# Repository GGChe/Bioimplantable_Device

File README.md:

# Bioimplantable_Device

For a brain implant, there are several limitations in terms of size, power and mechanical properties that may be considered. With the use of optoelectronic techniques, we achieved an ultra-small and fully implantable device that could be used for neurostimulation techniques. Moreover, a Wireless Power Transfer (WPT) system for powering the final LED was also devised to provide a demonstration. The proposed design in this study combines optimal size and practicality given the mechanical constraints of this implant typology. We have applied a modular design approach to the design of this device considering three modules: antenna, conditioner circuit and shank. The implant was designed by using a flexible substrate such as Polyimide. Thin biocompatible encapsulation was also provided for chronic implantation. In addition, simulation of mechanical forces acting on the implant and shank will be carried out to validate a viable shank conformation-encapsulation combination that will safely work under operational stress with a satisfactory margin of safety.

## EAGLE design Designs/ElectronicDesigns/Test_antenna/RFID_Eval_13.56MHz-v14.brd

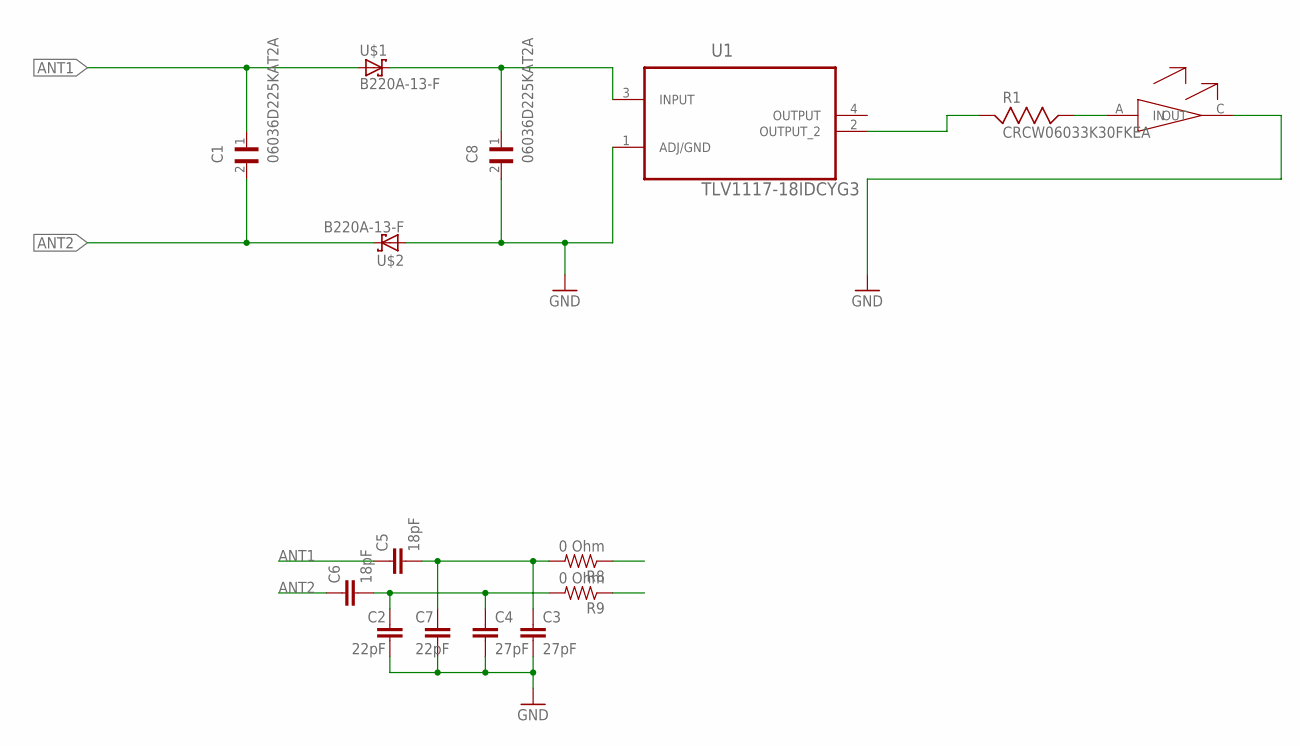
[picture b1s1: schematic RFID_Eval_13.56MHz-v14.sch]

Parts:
C1, C8: 06036D225KAT2A; CAPC1608X90
C2, C7: 22pF; 0402-CAP
C3, C4: 27pF; 0402-CAP
C5, C6: 18pF; 0402-CAP
R1: CRCW06033K30FKEA; RESC1608X55
R8, R9: 0 Ohm; 0402-RES
U1: TLV1117-18IDCYG3; SOT230P700X180-4N
U$1, U$2: B220A-13-F; SMA-DIODE
U$3: LED; LEDM1608X80

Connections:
ANT1: C1.1, C5.1, U$1.1 (A)
ANT2: C1.2, C6.1, U$2.2 (C)
GND: C2.2, C3.2, C4.2, C7.2, C8.2, U1.1 (ADJ/GND), U$2.1 (A), U$3.C (OUT)
unnamed: R1.1, U1.2 (OUTPUT_2)
unnamed: R1.2, U$3.A (IN)
unnamed: C8.1, U1.3 (INPUT), U$1.2 (C)
unnamed: C3.1, C5.2, C7.1, R8.2
unnamed: C2.1, C4.1, C6.2, R9.2

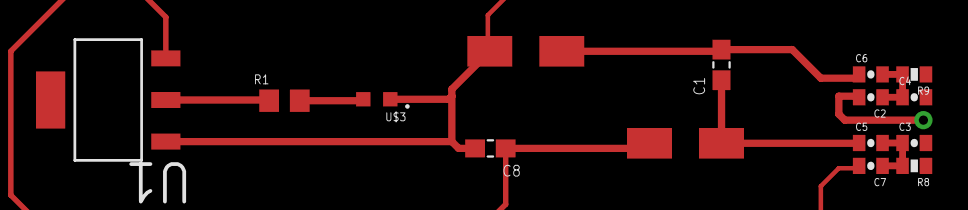
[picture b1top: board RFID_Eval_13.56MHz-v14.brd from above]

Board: 2 copper layers, 15 parts (0 on the bottom side), 8 nets.

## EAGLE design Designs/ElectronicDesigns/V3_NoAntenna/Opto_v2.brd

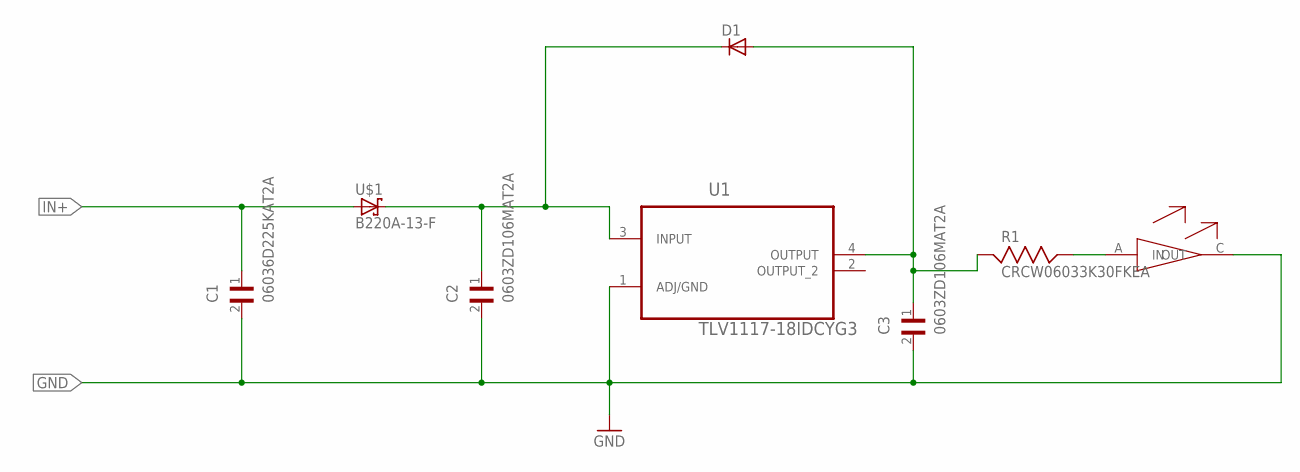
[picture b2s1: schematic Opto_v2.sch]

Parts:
C1: 06036D225KAT2A; CAPC1608X90
C2, C3: 0603ZD106MAT2A; CAPC1608X90
D1: BYS10; SOD106A
R1: CRCW06033K30FKEA; RESC1608X55
U1: TLV1117-18IDCYG3; SOT230P700X180-4N
U$1: B220A-13-F; SMA-DIODE
U$3: LED; LEDM1608X80

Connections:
GND: C1.2, C2.2, C3.2, U1.1 (ADJ/GND), U$3.C (OUT)
IN+: C1.1, U$1.1 (A)
unnamed: R1.2, U$3.A (IN)
unnamed: C3.1, D1.A, R1.1, U1.4 (OUTPUT)
unnamed: C2.1, D1.K, U1.3 (INPUT), U$1.2 (C)

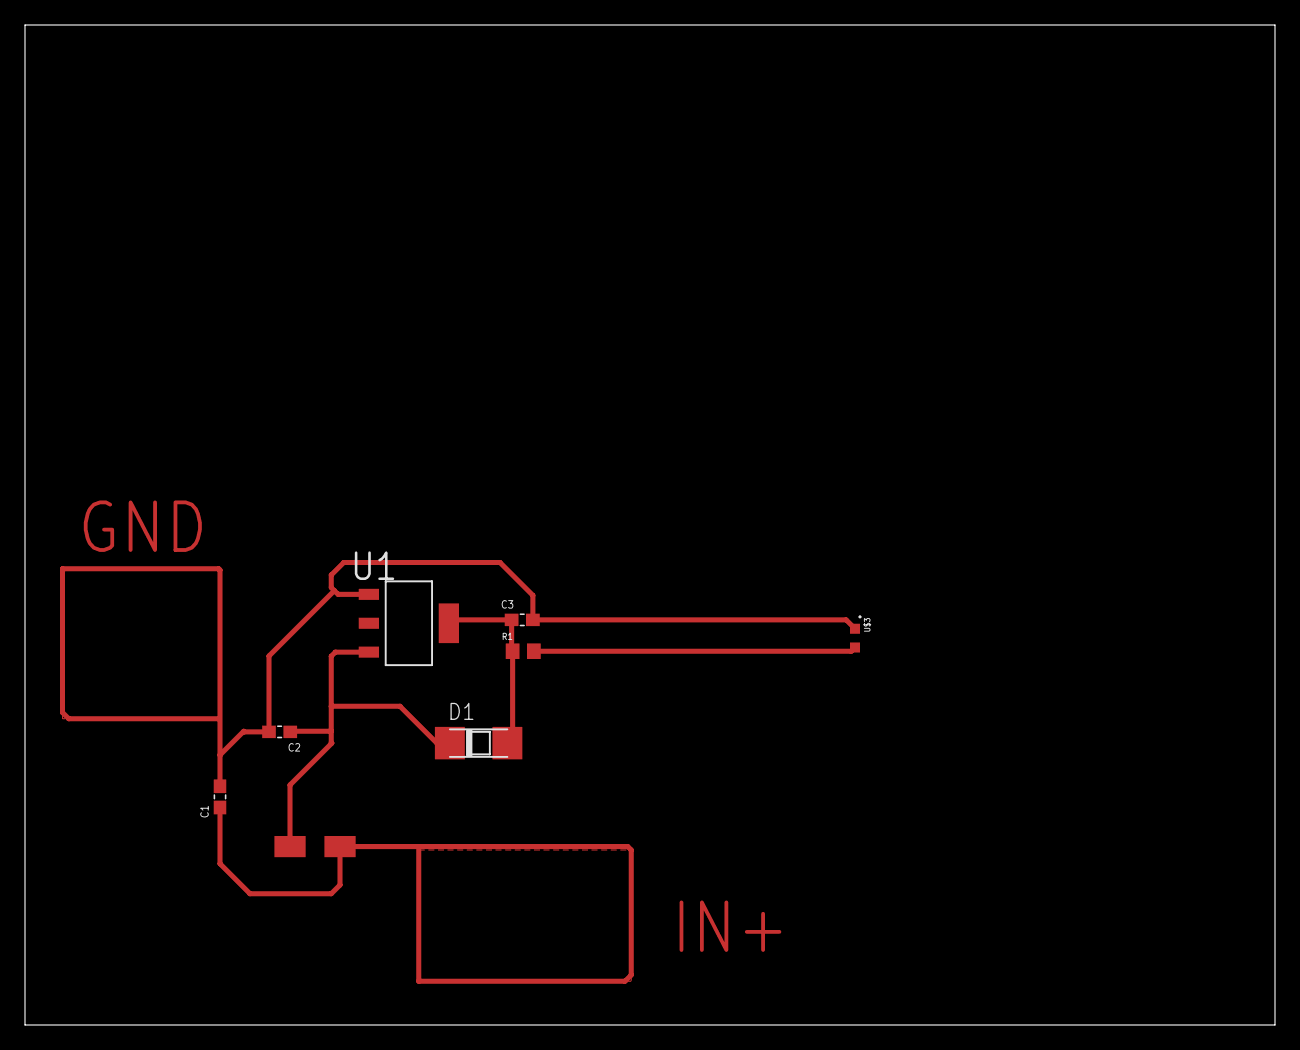
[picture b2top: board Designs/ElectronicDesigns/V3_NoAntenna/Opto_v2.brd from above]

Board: 2 copper layers, 100.0 x 80.0 mm, 8 parts (0 on the bottom side), 5 nets.

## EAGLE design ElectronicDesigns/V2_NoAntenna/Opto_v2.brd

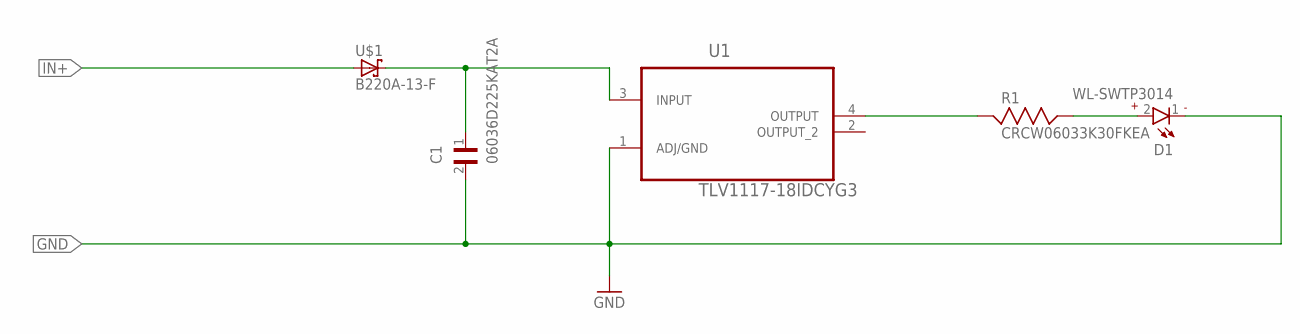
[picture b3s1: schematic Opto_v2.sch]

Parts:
C1: 06036D225KAT2A; CAPC1608X90
D1: WL-SWTP3014; WL-SWTP_3014
R1: CRCW06033K30FKEA; RESC1608X55
U1: TLV1117-18IDCYG3; SOT230P700X180-4N
U$1: B220A-13-F; SMA-DIODE

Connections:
GND: C1.2, D1.1, U1.1 (ADJ/GND)
IN+: U$1.1 (A)
unnamed: R1.1, U1.4 (OUTPUT)
unnamed: D1.2, R1.2
unnamed: C1.1, U1.3 (INPUT), U$1.2 (C)

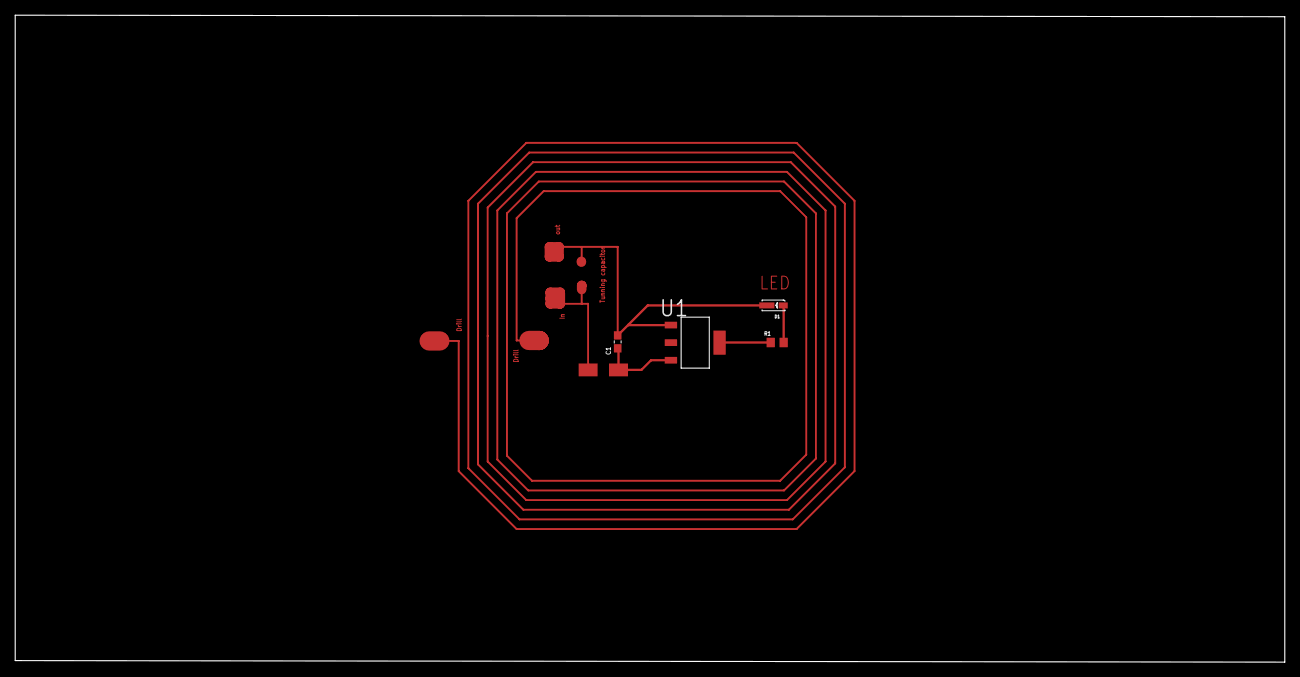
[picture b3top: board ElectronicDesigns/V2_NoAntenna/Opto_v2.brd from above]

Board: 2 copper layers, 167.0 x 85.1 mm, 5 parts (0 on the bottom side), 4 nets.

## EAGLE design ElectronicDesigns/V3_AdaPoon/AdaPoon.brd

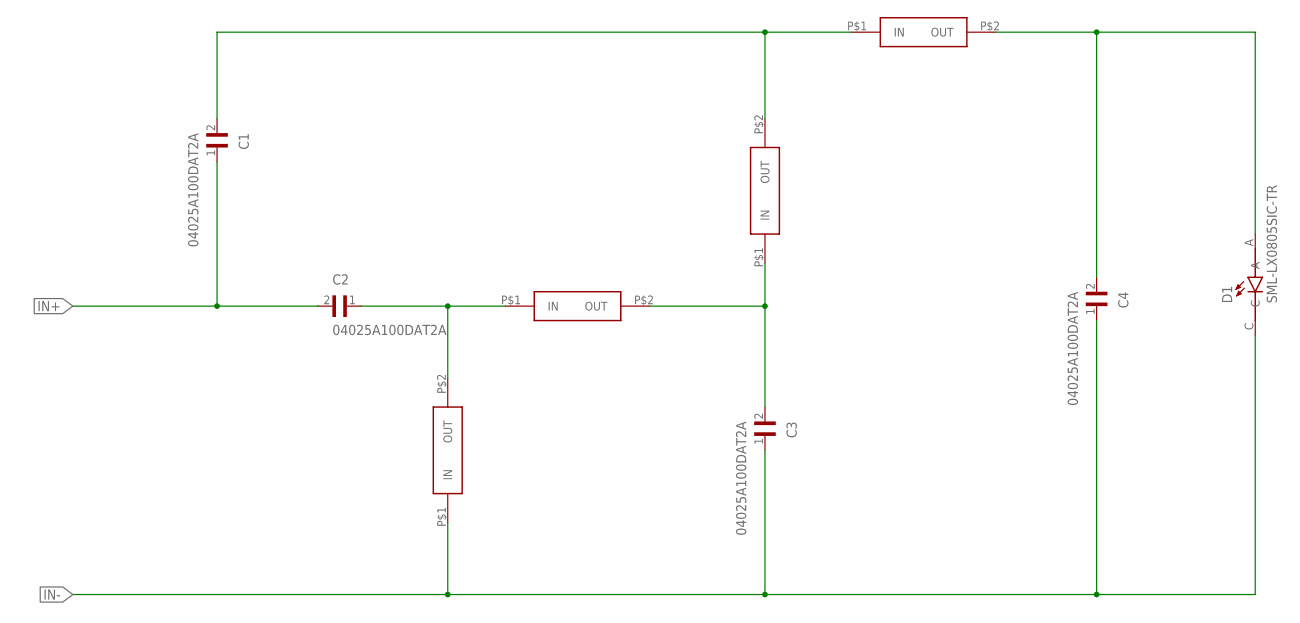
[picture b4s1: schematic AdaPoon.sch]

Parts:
C1, C2, C3, C4: 04025A100DAT2A; CAPC1005X56N
D1: SML-LX0805SIC-TR; LEDC2012X120N
U$1, U$2, U$3, U$4: SCHOTTKY0402; 0402_MURATA

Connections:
IN+: C1.1, C2.2
IN-: C3.1, C4.1, D1.C, U$1.P$1 (IN)
unnamed: C2.1, U$1.P$2 (OUT), U$2.P$1 (IN)
unnamed: C1.2, U$3.P$2 (OUT), U$4.P$1 (IN)
unnamed: C3.2, U$2.P$2 (OUT), U$3.P$1 (IN)
unnamed: C4.2, D1.A, U$4.P$2 (OUT)

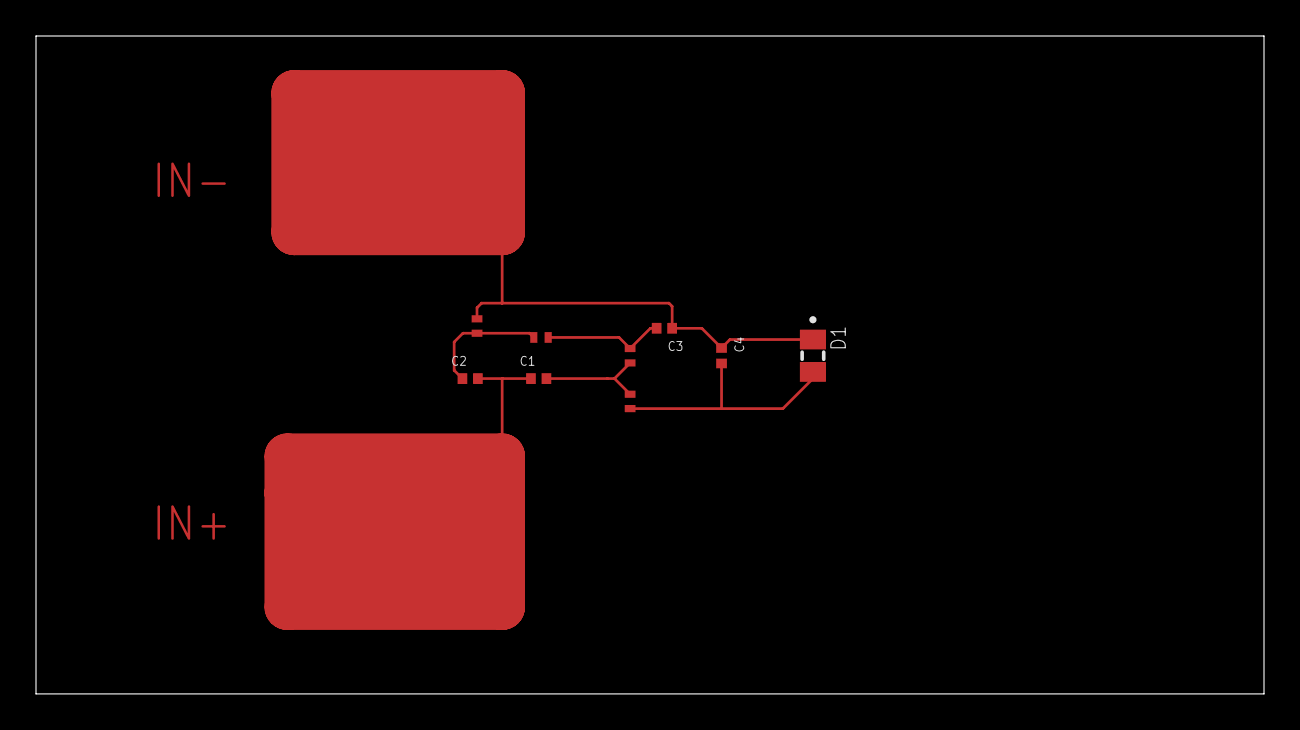
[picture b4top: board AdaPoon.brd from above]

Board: 2 copper layers, 68.2 x 36.6 mm, 9 parts (0 on the bottom side), 6 nets.

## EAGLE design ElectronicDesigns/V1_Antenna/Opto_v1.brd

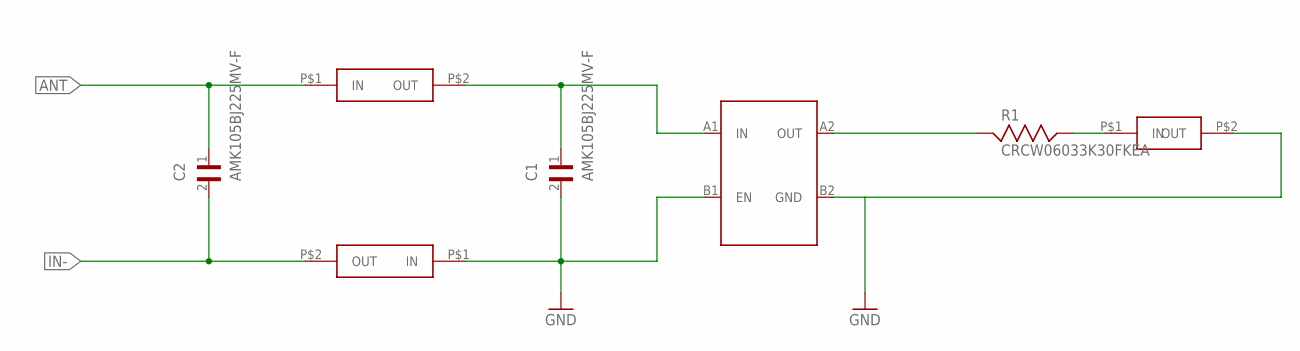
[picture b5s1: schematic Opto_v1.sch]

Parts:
C1, C2: AMK105BJ225MV-F; CAPC1005X55N
R1: CRCW06033K30FKEA; RESC1608X55
U$1: BGA4C4; BGA4C40P2X2_84X84X60N
U$2, U$3: SCHOTTKY0402; 0402_MURATA
U$4: CREE-TR2227

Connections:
GND: C1.2, U$1.B1 (EN), U$1.B2 (GND), U$3.P$1 (IN), U$4.P$2 (OUT)
IN+: C2.1, U$2.P$1 (IN)
IN-: C2.2, U$3.P$2 (OUT)
unnamed: R1.1, U$1.A2 (OUT)
unnamed: R1.2, U$4.P$1 (IN)
unnamed: C1.1, U$1.A1 (IN), U$2.P$2 (OUT)

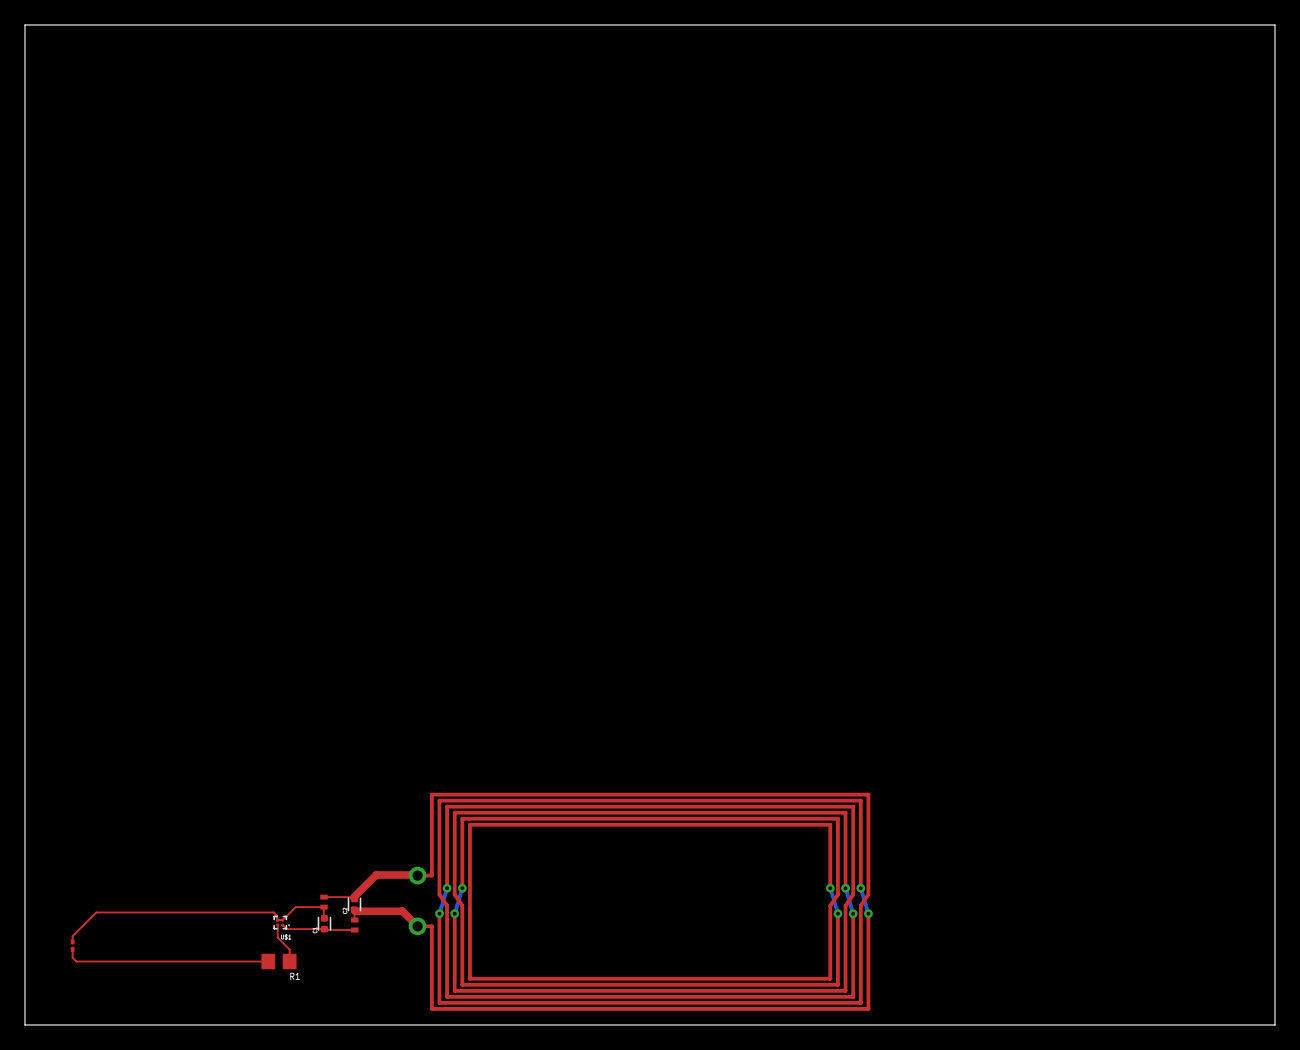
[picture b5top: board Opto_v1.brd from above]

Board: 2 copper layers, 100.0 x 80.0 mm, 7 parts (0 on the bottom side), 6 nets.

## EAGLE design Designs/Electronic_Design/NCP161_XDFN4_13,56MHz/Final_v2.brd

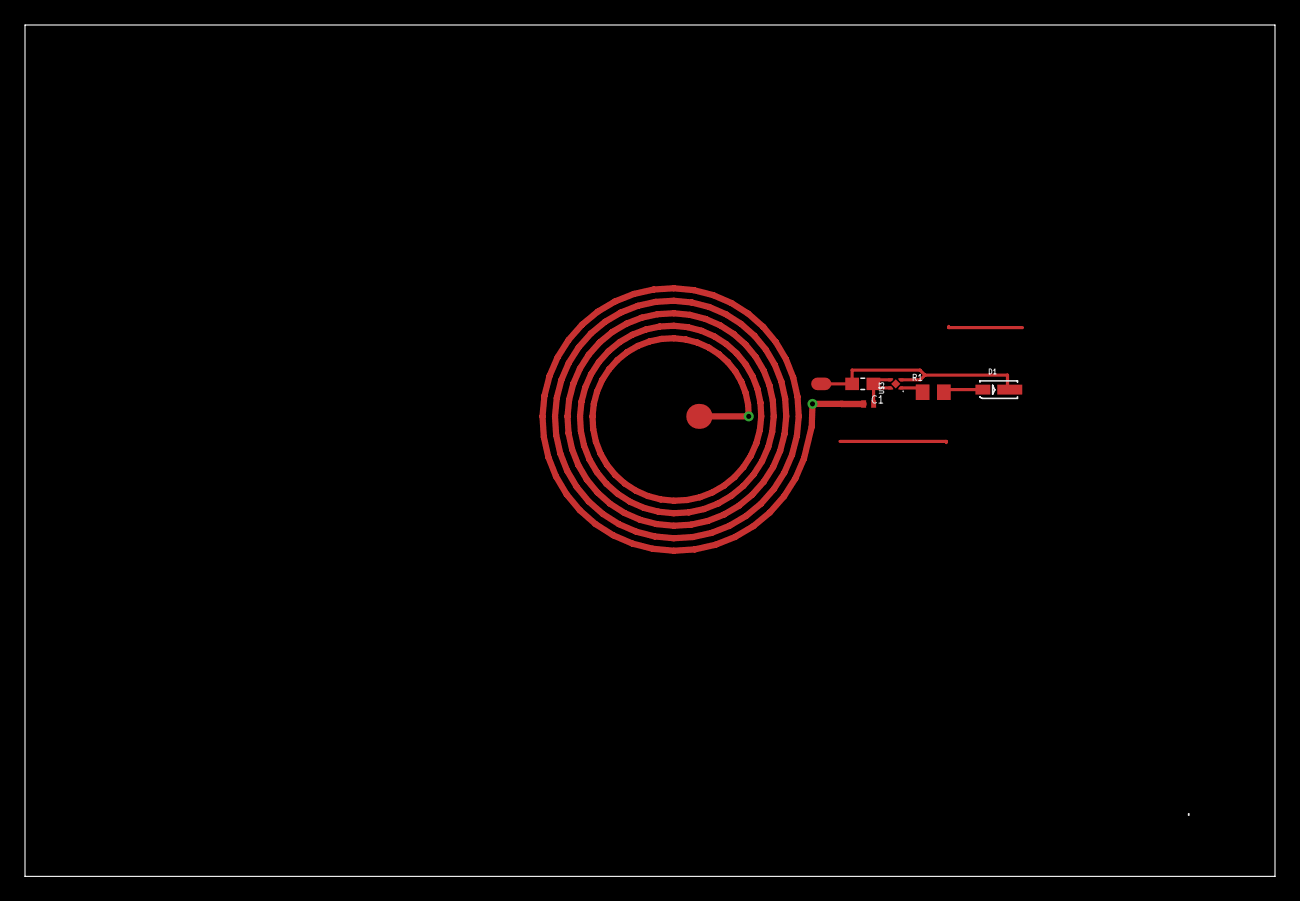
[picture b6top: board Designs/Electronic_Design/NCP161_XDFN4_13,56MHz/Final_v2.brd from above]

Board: 2 copper layers, 100.0 x 68.1 mm, 5 parts (0 on the bottom side), 4 nets.

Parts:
C1: 06036D225KAT2A; CAPC1608X90
D1: WL-SWTP3014; WL-SWTP_3014
R1: CRCW06033K30FKEA; RESC1608X55
U$2: SCHOTTKY0402; 0402_MURATA
U$3: NCP161_711AJ; REG_NCP160AMX180TBG

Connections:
GND: C1.2, D1.1, U$3.2
IN: C1.1, U$2.P$2, U$3.3, U$3.4
unnamed: D1.2, R1.2
OUT: R1.1, U$3.1

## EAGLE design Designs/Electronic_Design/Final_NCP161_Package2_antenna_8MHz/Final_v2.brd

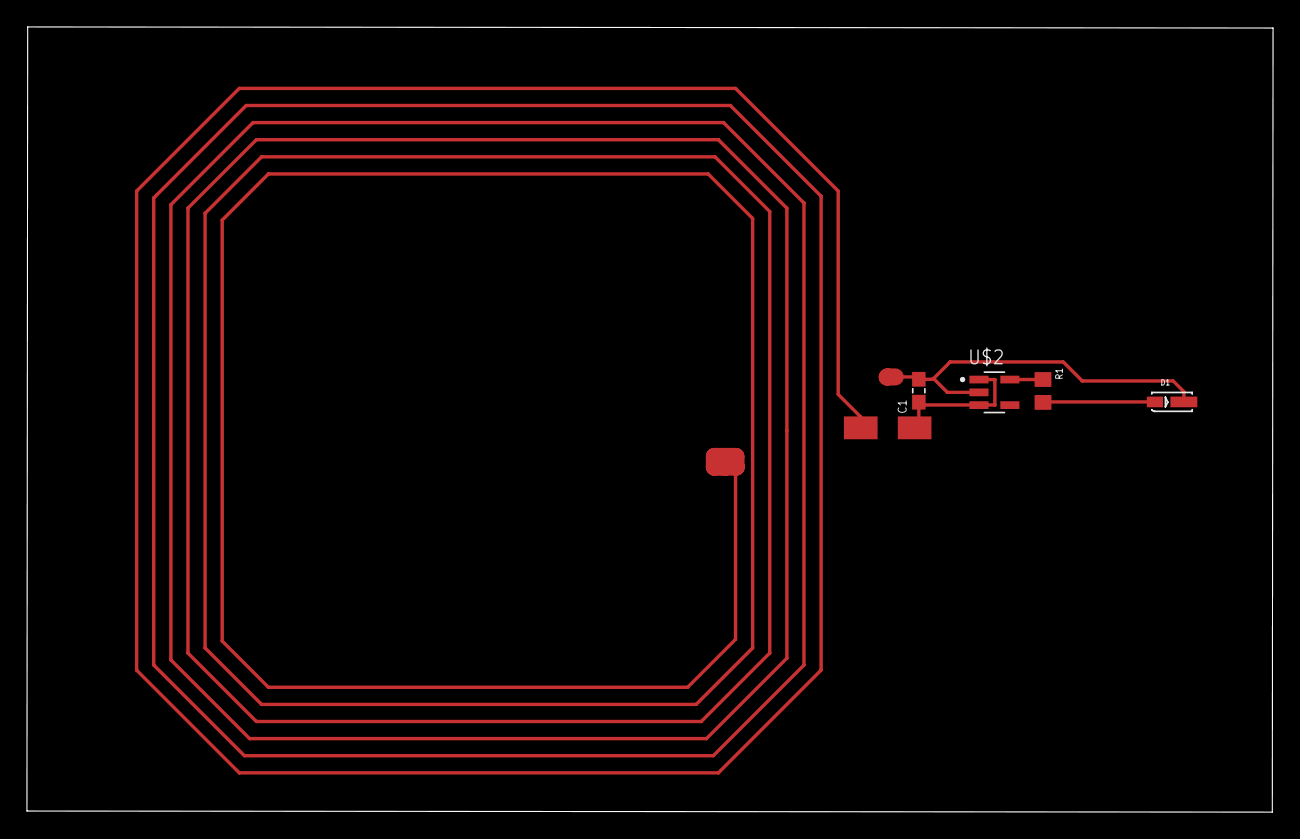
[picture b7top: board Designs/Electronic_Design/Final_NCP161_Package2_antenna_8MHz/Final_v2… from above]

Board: 2 copper layers, 92.5 x 58.3 mm, 5 parts (0 on the bottom side), 4 nets.

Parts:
C1: 06036D225KAT2A; CAPC1608X90
D1: WL-SWTP3014; WL-SWTP_3014
R1: CRCW06033K30FKEA; RESC1608X55
U$1: B220A-13-F; SMA-DIODE
U$2: NCV8161; SOP95P275X110-5N

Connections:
GND: C1.2, D1.1, U$2.2
unnamed: R1.1, U$2.5
unnamed: D1.2, R1.2
unnamed: C1.1, U$1.2, U$2.1, U$2.3

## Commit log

2019-05-07 Uploading designs files
2019-05-07 Folder management
2019-05-09 Update gerbers
2019-05-11 Updated gerbers
2019-05-12 Update PCB Components
2019-05-12 Printings
2019-05-13 Printing
2019-05-13 antenna designs
2019-05-13 Presentation for group meeting the 15th of May!
2019-05-13 Presentation for Rupam prepared
2019-05-14 Presentation for MeLAB meeting
2019-05-14 First try with antenna :)
2019-05-14 antenna design
2019-05-14 Presentation
2019-05-15 PCB Version 2 Printing
2019-05-17 antenna-circuit assembled
2019-05-17 Information about ceramic antennas and neuran interfaces
2019-05-17 modify antenna
2019-05-18 Proof of concept
2019-05-19 Preliminary report
2019-05-19 Preliminary report with gantt chart
2019-05-19 SMT Antenna design from Sparkfun
2019-05-19 article to print
2019-05-19 Paper of J. Rogers
2019-05-20 Printing modified
2019-05-21 schematic and pcb files
2019-05-21 Circuit modified for antenna of Sparkfun
2019-05-21 Initial Circuit Version
2019-05-22 Personal Folders
2019-05-22 Preliminary report updated
2019-05-23 Create KayaUke
2019-05-23 Create a
2019-05-23 Create Readme
    These are good articles that show how Shank and Electrodes can be modelled and simulated:
2019-05-23 Add files via upload
    Can you embed this below the welcome readme Gabriel?
2019-05-27 final version
2019-05-27 Upload Circuit
2019-05-27 Uptaded Circuit
2019-05-29 Update circuit with NCP161_711AJ
2019-05-30 gui guidebook
2019-05-30 update repository
2019-06-03 DXF file from antenna's design
2019-06-03 Update!
2019-06-06 Updated folders
2019-06-06 Final version of the circuit with antenna
2019-06-07 NFC Charging
2019-06-10 DXF upload for the circuit
2019-06-11 Rearrangement
2019-06-11 Update 11/06
2019-06-12 Presentations vor MSc meeting and MELAB meeting
2019-06-14 Update 14-06-2019
2019-06-16 Circuits Updated
2019-06-17 PCB Printing
2019-06-20 Update pictures
2019-06-29 Update 29-06
2019-07-02 Pictures from lab tests and microscope
2019-07-03 Pictures
2019-10-31 Final update
2019-11-04 Update repository 4-11-2019
